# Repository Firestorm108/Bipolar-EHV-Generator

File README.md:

# Bipolar-EHV-Generator
An extreme high voltage generator that utilizes a bipolar setup to effectively create a 300kV+ voltage difference.

# How does it work?

The custom ZVS driver drives the self-wound HV AC transformer. That transformer is connected to both inputs of voltage mulitpliers.
By configuring each multiplier to output a +HV and the other to do a -HV, it is no longer a +HV - GND difference, but +HV -HV difference.

# PCB Pictures

# Bill of Materials

| Item                               |    Price | Link                                                                                                         |
| ---------------------------------- | -------: | ------------------------------------------------------------------------------------------------------------ |
| White PLA                          |      $13 | [Amazon](https://www.amazon.com/SUNLU-Printer-Filament-1-75mm-Printers/dp/B0BD7K5SQK/)                       |
| Kapton Tape                        |      $10 | [Amazon](https://www.amazon.com/Hxtape-Temperature-Polyimide-Printing-Soldering/dp/B07D5RRXTS/)              |
| 32 AWG Magnet Wire                 |      $13 | [Amazon](https://www.amazon.com/BNTECHGO-AWG-Magnet-Wire-Transformers/dp/B07JBQQR38/)                        |
| Transformer Core                   |      $23 | [Amazon](https://www.amazon.com/5pairs-UY1658-Transformer-ferrite-Material/dp/B0146OG8VK/r)                  |
| 16 AWG                             |       $8 | [Amazon](https://www.amazon.com/Silicone-Electrical-Cable%EF%BC%8810ft-Temperature-Resistant/dp/B0D93K21TN/) |
| Momentary Push Button              |       $3 | [AliExpress](https://www.aliexpress.us/item/3256812230348809.html)                                           |
| 40 × 2CL77 Diodes                  |      $13 | [AliExpress](https://www.aliexpress.us/item/3256802425242911.html)                                           |
| 40 × 20 kV 1 nF Capacitors         |      $14 | [AliExpress](https://www.aliexpress.us/item/3256809649447491.html)                                           |
| 24 V 20 A SMPS                     |      $22 | [Amazon](https://www.amazon.com/HPMN-24V-15A-360W-Transformer/dp/B0DPKJPB5P)                                 |
| Mains Cable                        |       $4 | [AliExpress](https://www.aliexpress.us/item/3256802936747637.html)                                           |
| IRFP250 MOSFETs                    |       $6 | [AliExpress](https://www.aliexpress.us/item/3256806932452420.html)                                           |
| 470 Ω 2 W Resistors                |       $2 | [AliExpress](https://www.aliexpress.us/item/3256802900888178.html)                                           |
| 0.47 µH 10 A Inductor              |       $6 | [AliExpress](https://www.aliexpress.us/item/3256806537093956.html)                                           |
| 2-Pin Screw Terminals              |       $3 | [AliExpress](https://www.aliexpress.us/item/3256806674476213.html)                                           |
| 3-Pin Screw Terminals              |       $4 | [AliExpress](https://www.aliexpress.us/item/3256806674476213.html)                                           |
| 1N4742A 12 V Zener Diodes          |       $1 | [AliExpress](https://www.aliexpress.us/item/2255799836200735.html)                                           |
| UF4007 400 V Fast-Switching Diodes |       $2 | [AliExpress](https://www.aliexpress.us/item/2255800018624086.html)                                           |
| 0.68 µF Film Capacitors            |       $3 | [AliExpress](https://www.aliexpress.us/item/3256801916333851.html)                                           |
| 50 V 1000 µF Electrolytics         |       $5 | [AliExpress](https://www.aliexpress.us/item/3256811625053645.html)                                           |
| Multiplier PCB                     |       $8 | JLCPCB                                                                                                       |
| ZVS PCB                            |      $16 | JLCPCB                                                                                                       |
| JLC Shipping                       |      $15 | JLCPCB                                                                                                       |
| **Total**                          | **$194** |                                                                                                              |

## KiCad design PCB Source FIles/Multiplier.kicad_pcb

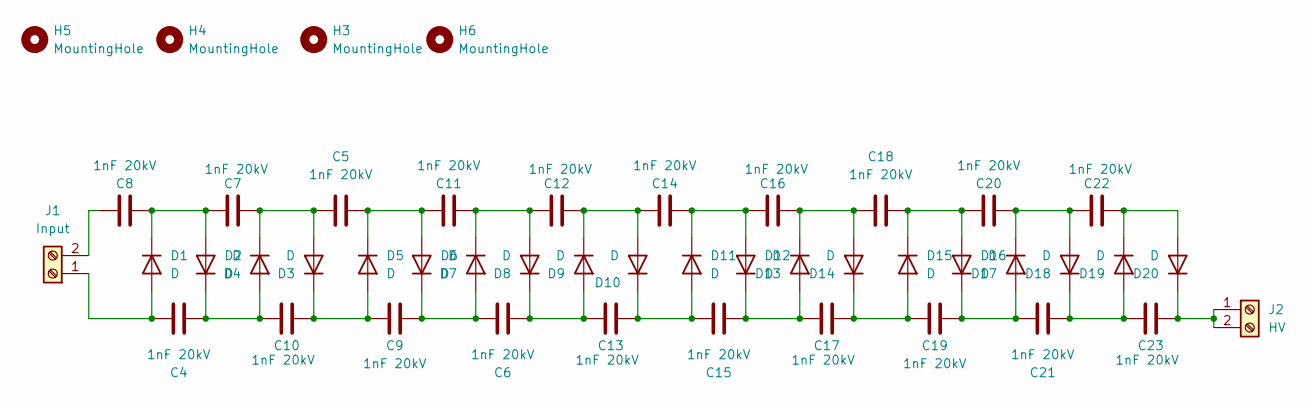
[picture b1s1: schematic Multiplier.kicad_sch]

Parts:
C4, C5, C6, C7, C8, C9, C10, C11, C12, C13, C14, C15, C16, C17, C18, C19, C20, C21, C22, C23: 1nF 20kV; C_Disc_D11.0mm_W5.0mm_P10.00mm
D1, D2, D3, D4, D5, D6, D7, D8, D9, D10, D11, D12, D13, D14, D15, D16, D17, D18, D19, D20: D; D_DO-41_SOD81_P12.70mm_Horizontal
H3, H4, H5, H6: MountingHole; MountingHole_3.2mm_M3
J1: Input; CONN-TH_2P-P9.50_HB9500-9.5-2P
J2: HV; CONN-TH_2P-P9.50_HB9500-9.5-2P

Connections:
unnamed: C4.2, D1.2 (A), J1.1
unnamed: C7.2, C8.1, D1.1 (K), D2.2 (A)
unnamed: C4.1, C10.1, D2.1 (K), D4.2 (A)
unnamed: C5.1, C7.1, D3.2 (A), D4.1 (K)
unnamed: C9.1, C10.2, D3.1 (K), D5.2 (A)
unnamed: C5.2, C11.2, D5.1 (K), D6.2 (A)
unnamed: C6.2, C9.2, D6.1 (K), D7.2 (A)
unnamed: C11.1, C12.2, D7.1 (K), D8.2 (A)
unnamed: C6.1, C13.1, D8.1 (K), D9.2 (A)
unnamed: C12.1, C14.2, D9.1 (K), D10.2 (A)
unnamed: C13.2, C15.2, D10.1 (K), D11.2 (A)
unnamed: C14.1, C16.2, D11.1 (K), D12.2 (A)
unnamed: C15.1, C17.1, D12.1 (K), D13.2 (A)
unnamed: C16.1, C18.1, D13.1 (K), D14.2 (A)
unnamed: C17.2, C19.1, D14.1 (K), D15.2 (A)
unnamed: C18.2, C20.2, D15.1 (K), D16.2 (A)
unnamed: C19.2, C21.2, D16.1 (K), D17.2 (A)
unnamed: C20.1, C22.2, D17.1 (K), D18.2 (A)
unnamed: C21.1, C23.1, D18.1 (K), D19.2 (A)
unnamed: C22.1, D19.1 (K), D20.2 (A)
unnamed: C23.2, D20.1 (K), J2.1, J2.2
unnamed: C8.2, J1.2

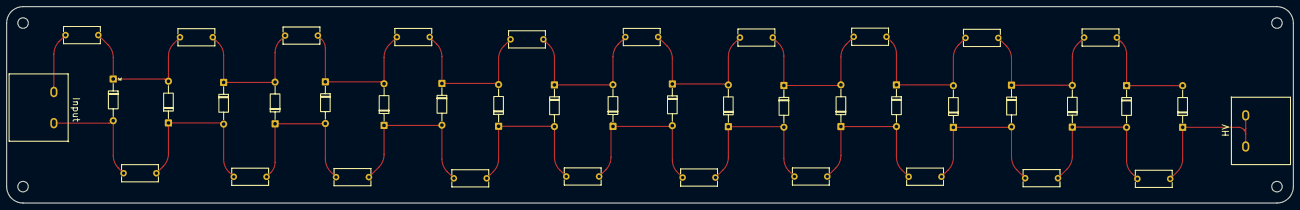
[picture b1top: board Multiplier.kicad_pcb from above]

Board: 2 copper layers, 392.1 x 59.8 mm, 46 parts (0 on the bottom side), 22 nets.

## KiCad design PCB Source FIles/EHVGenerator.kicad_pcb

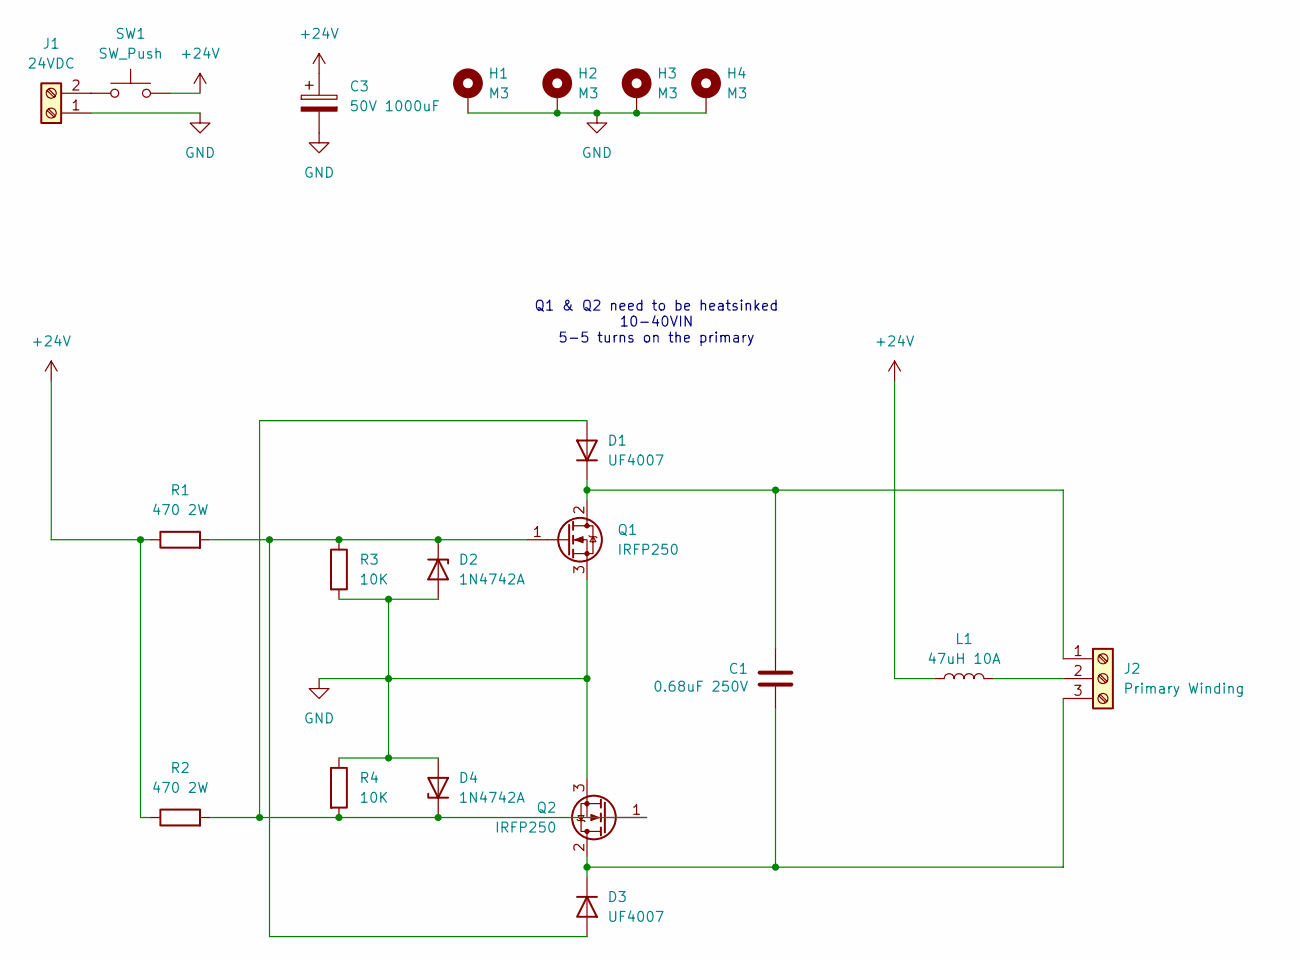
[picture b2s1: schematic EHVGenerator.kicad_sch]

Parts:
C1: 0.68uF 250V; C_Rect_L16.5mm_W5.0mm_P15.00mm_MKT
C3: 50V 1000uF; CP_Radial_D16.0mm_P7.50mm
D1, D3: UF4007; D_DO-41_SOD81_P10.16mm_Horizontal
D2, D4: 1N4742A; D_DO-41_SOD81_P10.16mm_Horizontal
H1, H2, H3, H4: M3; MountingHole_3.2mm_M3_Pad
J1: 24VDC; CONN-TH_2P-P9.50_HB9500-9.5-2P
J2: Primary Winding; CONN-TH_3P-P9.50_HB9500-9.5-3P
L1: 47uH 10A; L_Toroid_Vertical_L28.6mm_W14.3mm_P11.43mm_Bourns_5700
Q1, Q2: IRFP250; TO-247-3_Vertical
R1, R2: 470 2W; R_Axial_DIN0617_L17.0mm_D6.0mm_P20.32mm_Horizontal
R3, R4: 10K; R_Axial_DIN0207_L6.3mm_D2.5mm_P10.16mm_Horizontal
SW1: SW_Push; CONN-TH_2P-P9.50_HB9500-9.5-2P

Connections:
+24V: C3.1, L1.1, R1.1, R2.1, SW1.2
GND: C3.2, D2.2 (A), D4.2 (A), H1.1 (1_1), H2.1 (1_1), H3.1 (1_1), H4.1 (1_1), J1.1, Q1.3 (S), Q2.3 (S), R3.2, R4.1
unnamed: D1.2 (A), D4.1 (K), Q2.1 (G), R2.2, R4.2
unnamed: C1.2, D1.1 (K), J2.1, Q1.2 (D)
unnamed: D2.1 (K), D3.2 (A), Q1.1 (G), R1.2, R3.1
unnamed: C1.1, D3.1 (K), J2.3, Q2.2 (D)
unnamed: J1.2, SW1.1
unnamed: J2.2, L1.2

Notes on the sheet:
Q1 & Q2 need to be heatsinked 10-40VIN 5-5 turns on the primary

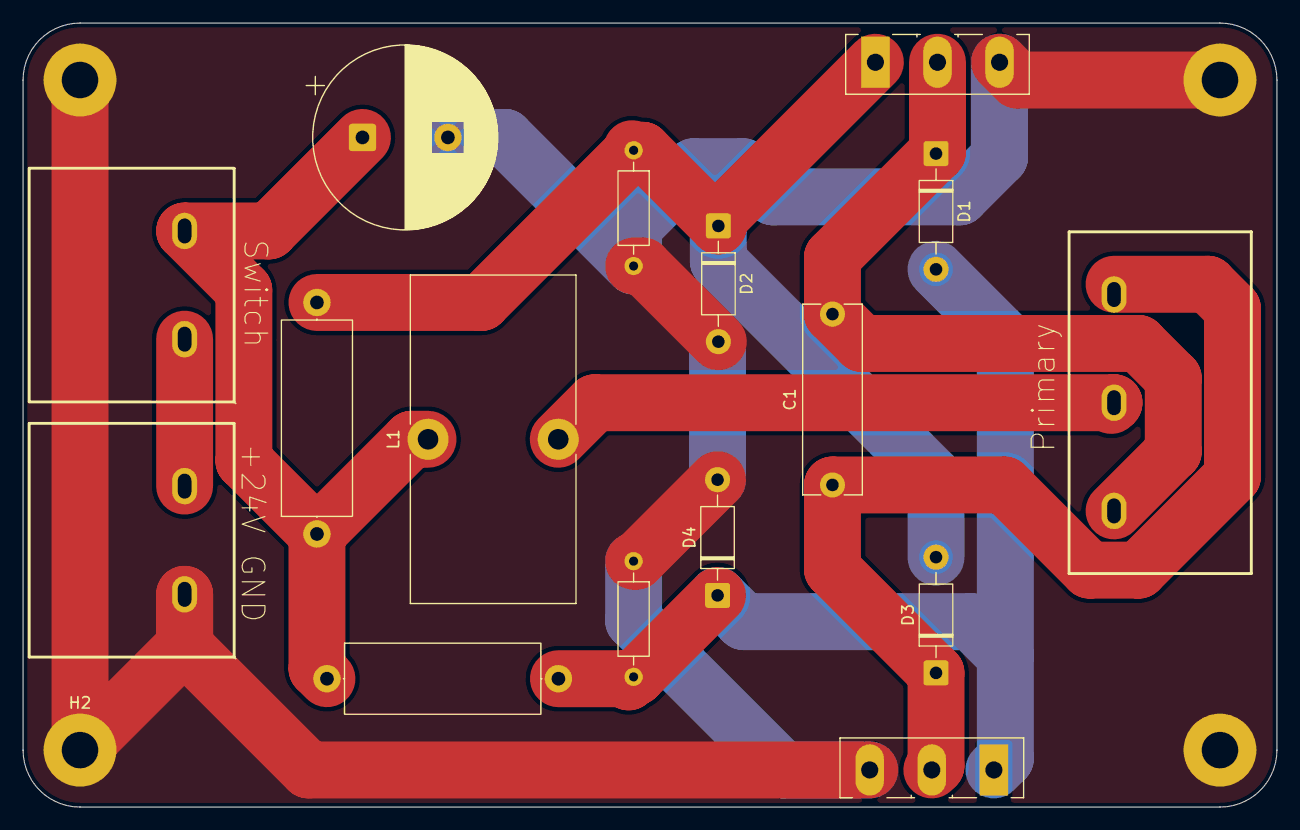
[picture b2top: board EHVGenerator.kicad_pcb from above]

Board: 2 copper layers, 110.1 x 68.8 mm, 20 parts (0 on the bottom side), 8 nets.

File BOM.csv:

Item,Price,Link
White PLA,$13,https://www.amazon.com/SUNLU-Printer-Filament-1-75mm-Printer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
Kapton Tape,$10,https://www.amazon.com/Hxtape-Temperature-Polyimide-Printing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
32AWG Magnet Wire,$13,https://www.amazon.com/BNTECHGO-AWG-Magnet-Wire-Transformers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
Transformer Core,$23,https://www.amazon.com/5pairs-UY1658-Transformer-ferrite-Mat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
16 AWG,$8,https://www.amazon.com/Silicone-Electrical-Cable%EF%BC%8810f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
,,
Momentary Push Button,$3,https://www.aliexpress.us/item/3256812230348809.html?
40 2CL77 Diodes,$13,https://www.aliexpress.us/item/3256802425242911.html
40 20kV 1nF Capacitors,$14,https://www.aliexpress.us/item/3256809649447491.html
,,
24V 20A SMPS,$22,https://www.amazon.com/HPMN-24V-15A-360W-Transformer/dp/B0DPKJPB5P
Mains Cable,$4,https://www.aliexpress.us/item/3256802936747637.html
,,
IRFP250 MOSFETs,$6,https://www.aliexpress.us/item/3256806932452420.html?
470 Ohm 2W Resistors,$2,https://www.aliexpress.us/item/3256802900888178.html?
0.47uH 10A Inductor,$6,https://www.aliexpress.us/item/3256806537093956.html
2 Pin Screw Terminals,$3,https://www.aliexpress.us/item/3256806674476213.html
3 Pin Screw Terminals,$4,https://www.aliexpress.us/item/3256806674476213.html
1N4742A 12V Zener Diodes,$1,https://www.aliexpress.us/item/2255799836200735.html?
UF4007 400V Fast Switching Diodes,$2,https://www.aliexpress.us/item/2255800018624086.html?
0.68uF Film Capacitors,$3,https://www.aliexpress.us/item/3256801916333851.html
50V 1000uF Electrolytics,$5,https://www.aliexpress.us/item/3256811625053645.html?
,,
Multiplier PCB,$8,JLCPCB
ZVS PCB,$16,JLCPCB
JLC Shipping,$15,JLCPCB
,,
Total,$194,
